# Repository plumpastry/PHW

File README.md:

# **P**lum's **H**ard**W**are

PHW-Board#-Part#-Revision#

## PHW-1-1-2:

NFC smartwatch development board

## PHW-1-1-1:

NFC smartwatch original board - infeasible manual assembly due to STM32WL

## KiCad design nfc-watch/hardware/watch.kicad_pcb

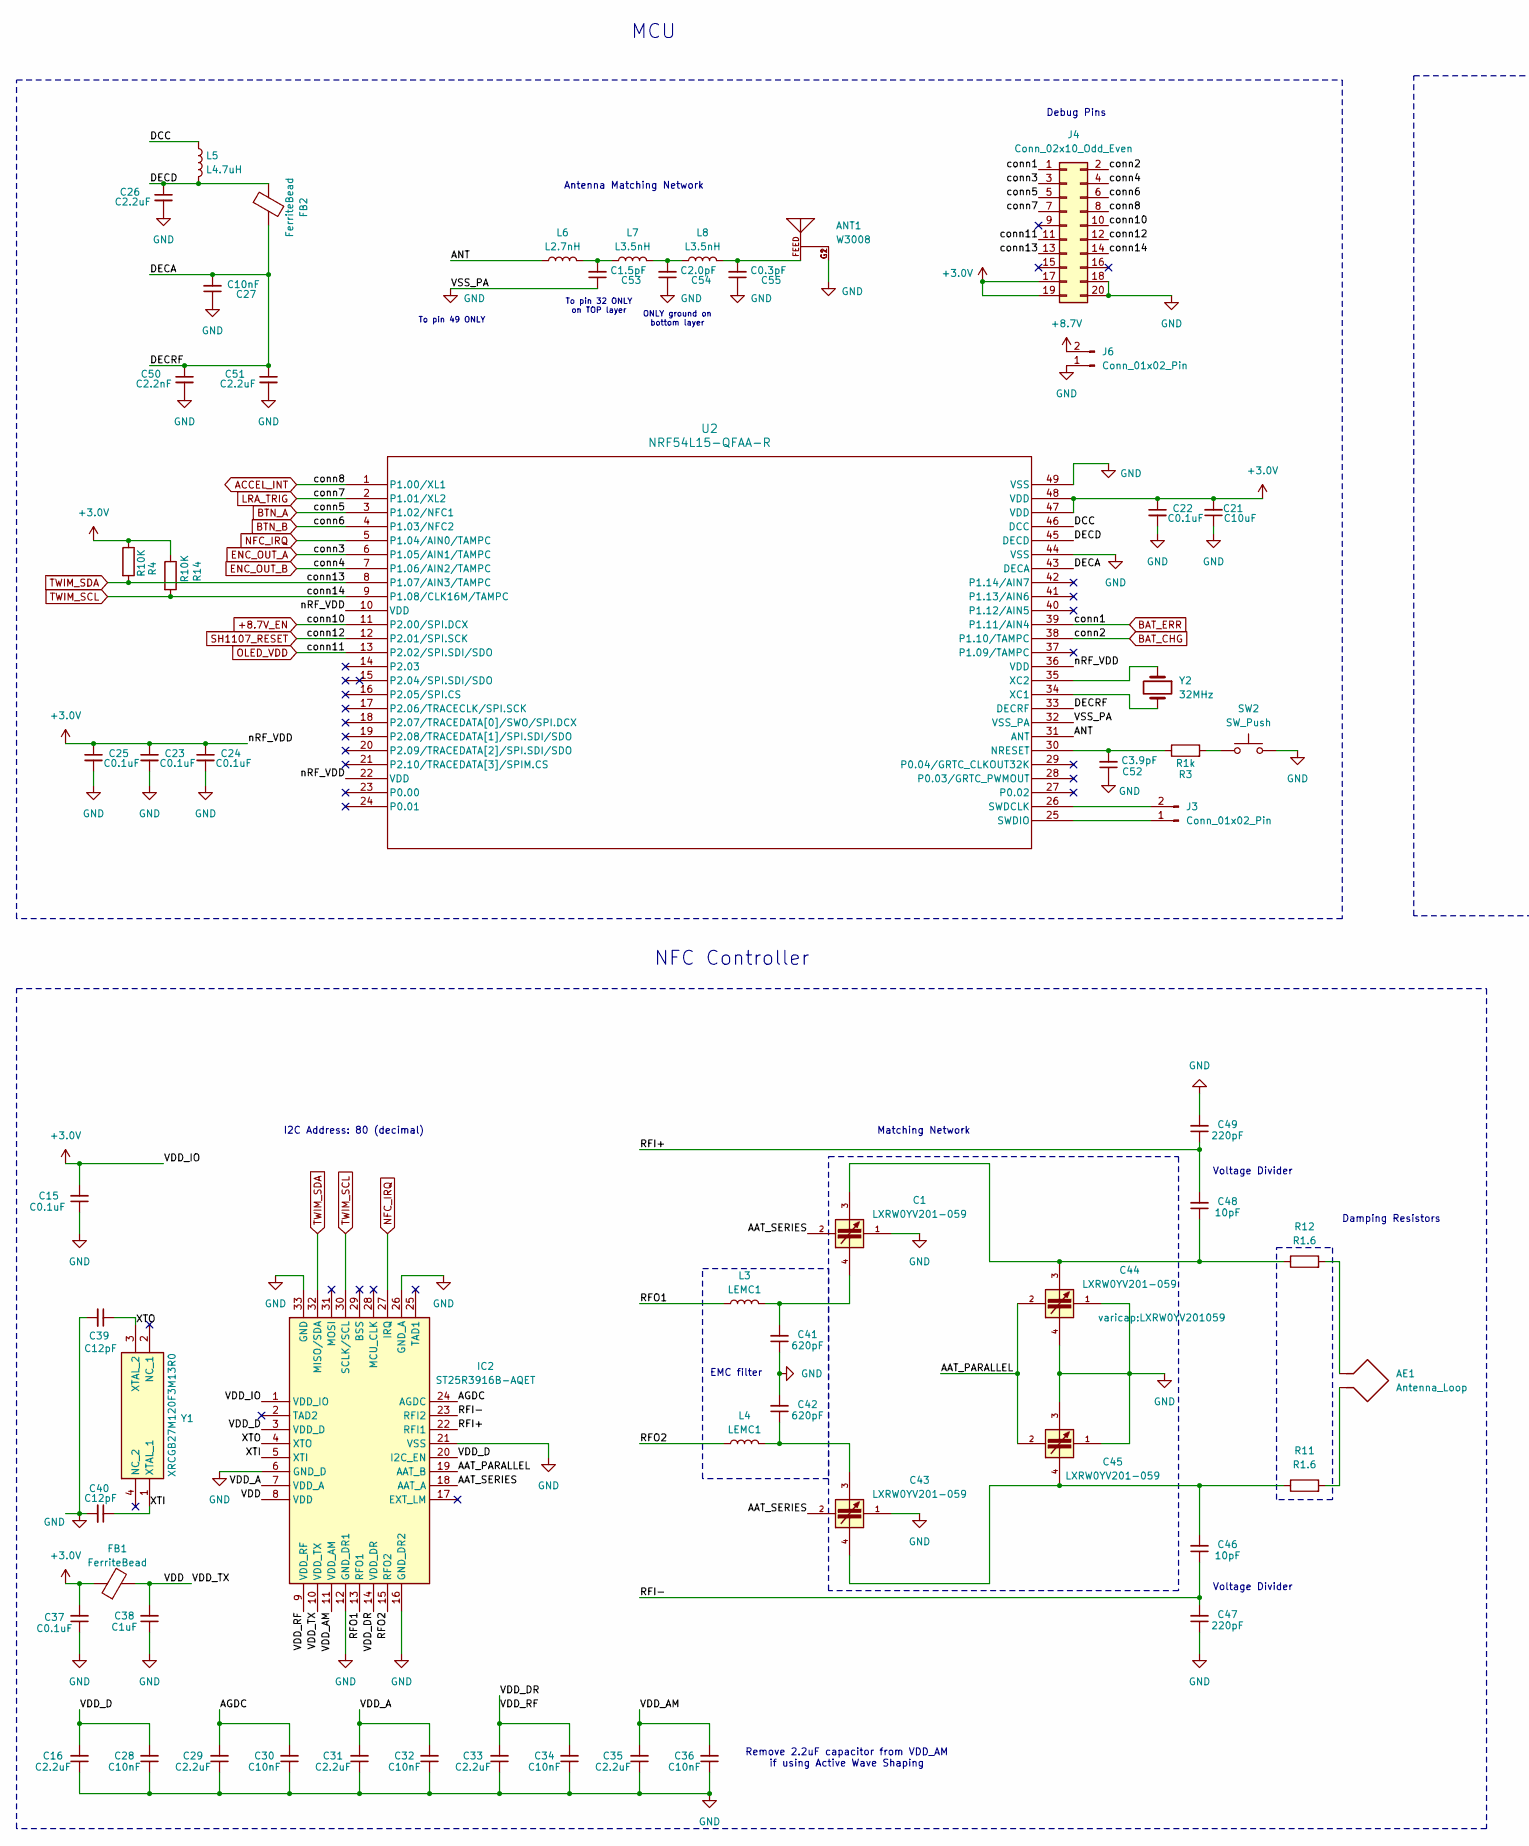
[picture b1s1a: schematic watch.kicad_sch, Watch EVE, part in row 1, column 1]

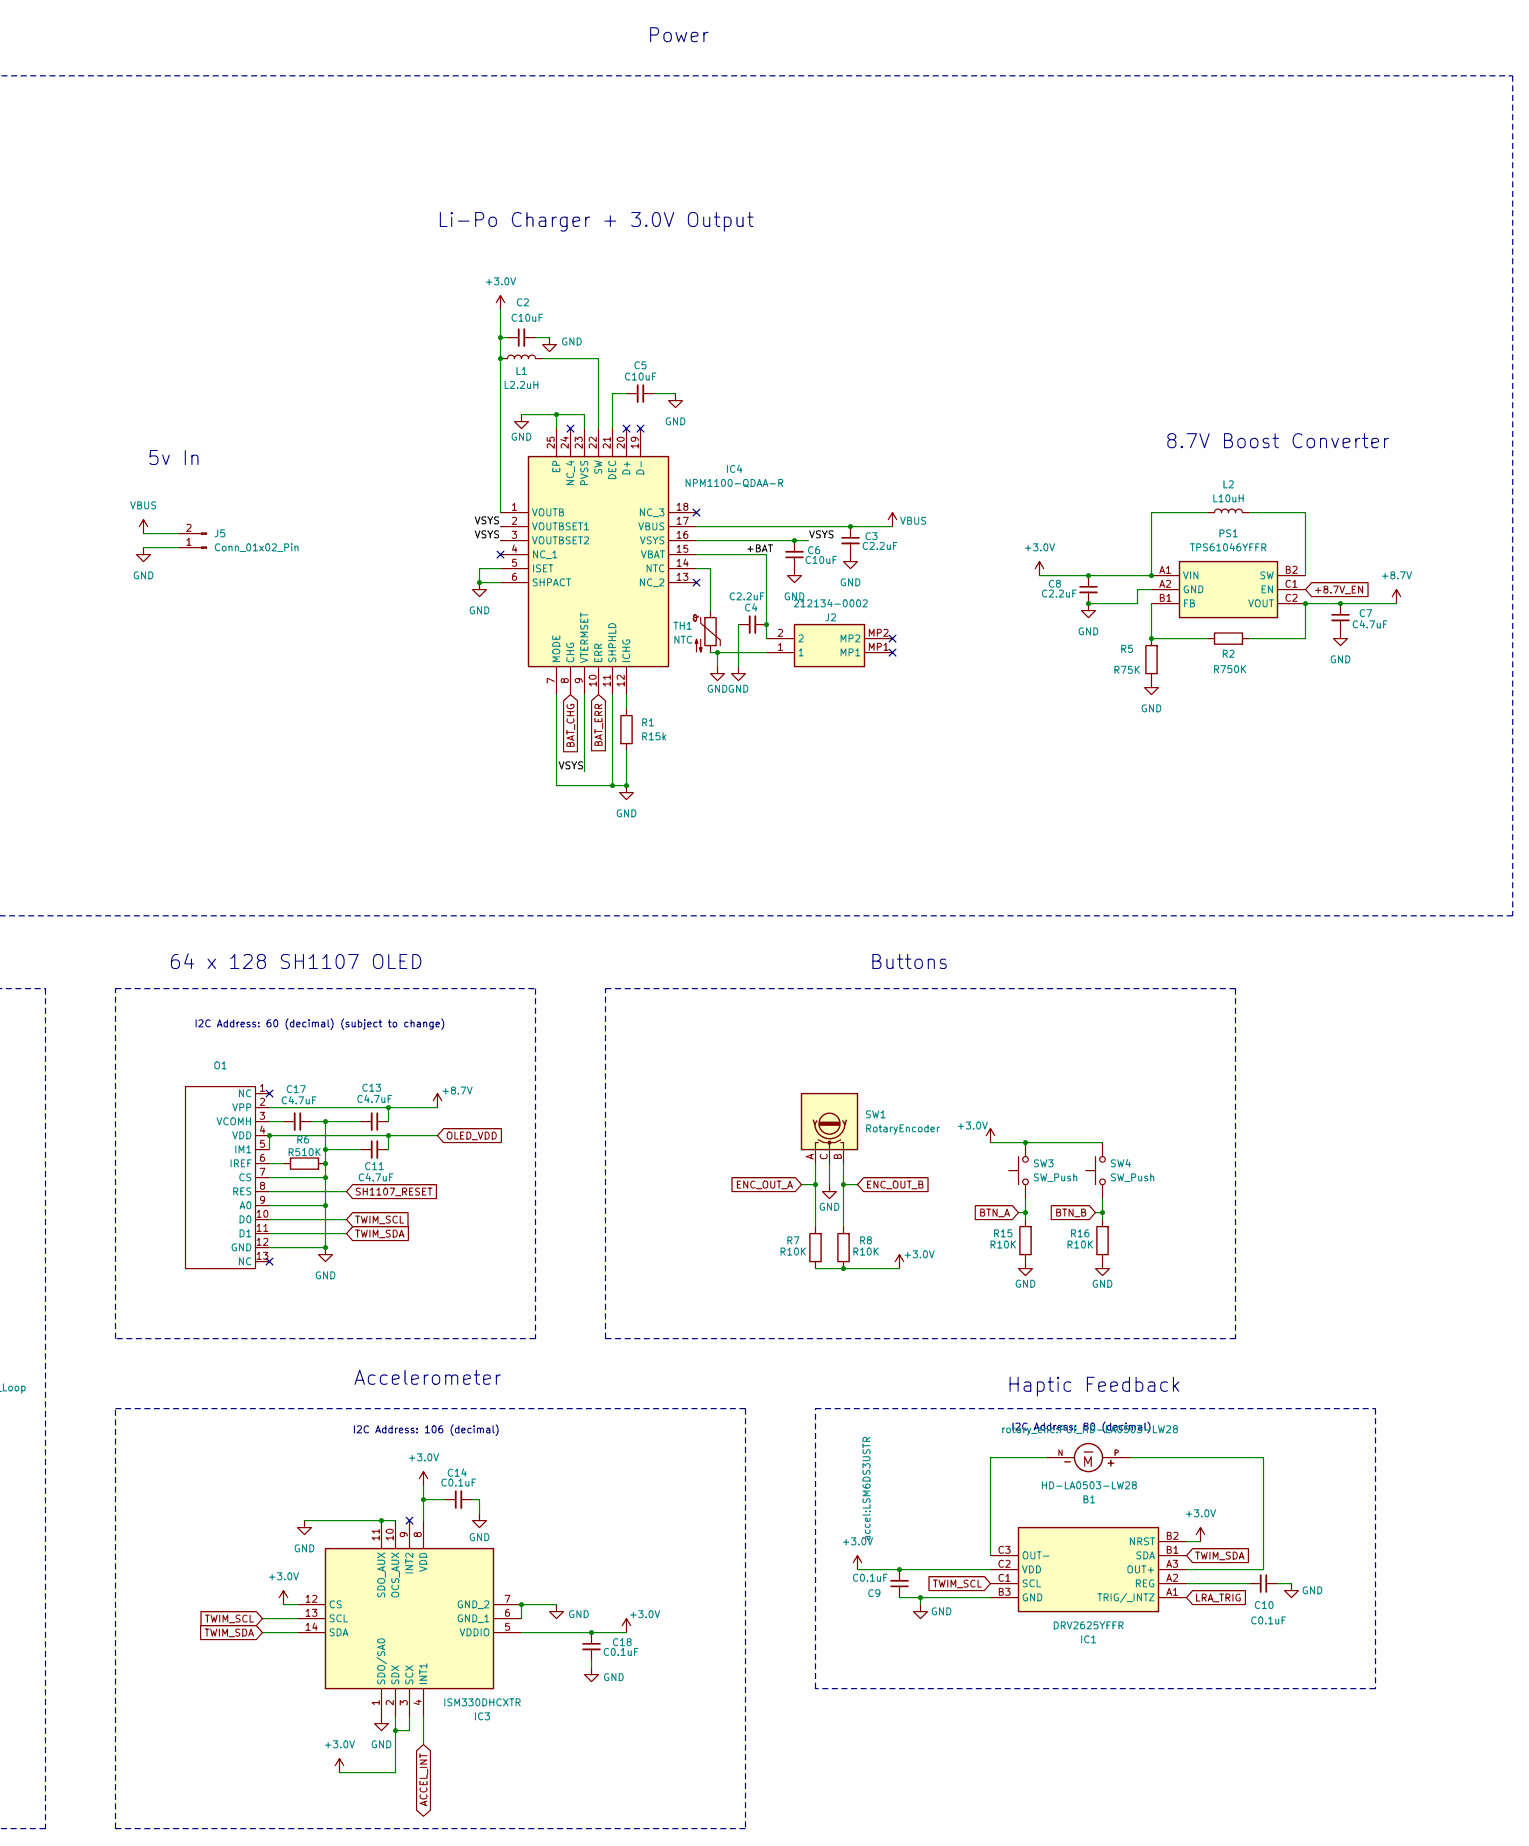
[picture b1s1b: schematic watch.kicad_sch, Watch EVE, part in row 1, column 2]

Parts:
AE1: Antenna_Loop; C_0603_1608Metric
ANT1: W3008; ANTENNA_W3008
B1: HD-LA0503-LW28; PUI_HD-LA0503-LW28; PARTREV A
C1, C43, C44, C45: LXRW0YV201-059; LXRW0YV201059; PARTREV July, 2018
C2, C5, C6, C21: C10uF; C_0402_1005Metric
C3, C4, C8, C26, C51: C2.2uF; C_0402_1005Metric
C7, C11, C13, C17: C4.7uF; C_0402_1005Metric
C9, C10, C14, C15, C18, C22, C23, C24, C25, C37: C0.1uF; C_0402_1005Metric
C16, C29, C31, C33, C35: C2.2uF; C_0201_0603Metric
C27, C28, C30, C32, C34, C36: C10nF; C_0201_0603Metric
C38: C1uF; C_0402_1005Metric
C39, C40: C12pF; C_0402_1005Metric
C41, C42: 620pF; C_0402_1005Metric
C46, C48: 10pF; C_0402_1005Metric
C47, C49: 220pF; C_0402_1005Metric
C50: C2.2nF; C_0402_1005Metric
C52: C3.9pF; C_0402_1005Metric
C53: C1.5pF; C_0201_0603Metric
C54: C2.0pF; C_0201_0603Metric
C55: C0.3pF; C_0201_0603Metric
FB1, FB2: FerriteBead; L_0402_1005Metric
IC1: DRV2625YFFR; BGA9C40P3X3_147X133X62; Mouser Part Number 595-DRV2625YFFR
IC2: ST25R3916B-AQET; QFN50P500X500X60-33N-D; Mouser Part Number 511-ST25R3916B-AQET
IC3: ISM330DHCXTR; LSM6DS3USTR; Mouser Part Number 511-ISM330DHCXTR
IC4: NPM1100-QDAA-R; QFN50P400X400X90-25N-D; Mouser Part Number 949-NPM1100-QDAA-R
J2: 212134-0002; 2121340002; Mouser Part Number 538-212134-0002
J3, J5, J6: Conn_01x02_Pin; PinHeader_1x02_P2.54mm_Vertical
J4: Conn_02x10_Odd_Even; PinHeader_2x10_P2.54mm_Vertical
L1: L2.2uH; L_0805_2012Metric
L2: L10uH; L_1008_2520Metric
L3, L4: LEMC1; L_0402_1005Metric
L5: L4.7uH; L_0603_1608Metric
L6: L2.7nH; L_0201_0603Metric
L7, L8: L3.5nH; L_0201_0603Metric
O1: P0.7_FPC
PS1: TPS61046YFFR; BGA6C40P2X3_88X123X62; Mouser Part Number 595-TPS61046YFFR
R1: R15k; R_0402_1005Metric
R2: R750K; R_0402_1005Metric
R3: R1k; C_0402_1005Metric
R4, R7, R8, R14, R15, R16: R10K; R_0402_1005Metric
R5: R75K; R_0402_1005Metric
R6: R510K; R_0402_1005Metric
R11, R12: R1.6; R_0402_1005Metric
SW1: RotaryEncoder; alps_ec05e
SW2, SW3, SW4: SW_Push; SW_B3U-1100P
TH1: NTC; C_0201_0603Metric
U2: NRF54L15-QFAA-R; QFN-48-1EP_6x6mm_P0.4mm_EP4.6x4.6mm
Y1: XRCGB27M120F3M13R0; XRCGB; Mouser Part Number 81-XRCGB27M120F3M13R
Y2: 32MHz; Crystal_SMD_2016-4Pin_2.0x1.6mm

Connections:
+3.0V: C2.1, C8.1, C9.2, C14.1, C15.2, C18.1, C21.2, C22.1, C23.1, C24.1, C25.1, C37.2, FB1.1, IC1.B2 (NRST), IC1.C2 (VDD), IC2.1 (VDD_IO), IC3.2 (SDX), IC3.3 (SCX), IC3.5 (VDDIO), IC3.8 (VDD), IC3.12 (CS), IC4.1 (VOUTB), J4.17, J4.19, L1.1, L2.1, PS1.A1 (VIN), R4.1, R7.1, R8.1, R14.1, SW3.2, SW4.2, U2.10 (VDD), U2.22 (VDD), U2.36 (VDD), U2.47 (VDD), U2.48 (VDD)
+8.7V: C7.1, C13.1, J6.2, O1.2 (VPP), PS1.C2 (VOUT), R2.2
+8.7V_EN: J4.10, PS1.C1 (EN), U2.11 (P2.00/SPI.DCX)
/+BAT: C4.2, IC4.15 (VBAT), J2.2
/AAT_PARALLEL: C44.2, C45.2, IC2.19 (AAT_B)
/AAT_SERIES: C1.2, C43.2, IC2.18 (AAT_A)
/AGDC: C29.2, C30.2, IC2.24 (AGDC)
/ANT: L6.1, U2.31 (ANT)
/DCC: L5.1, U2.46 (DCC)
/DECA: C27.2, C50.1, C51.1, FB2.2, U2.33 (DECRF), U2.43 (DECA)
/DECD: C26.1, FB2.1, L5.2, U2.45 (DECD)
/RFI+: C48.2, C49.1, IC2.22 (RFI1)
/RFI-: C46.1, C47.2, IC2.23 (RFI2)
/RFO1: IC2.13 (RFO1), L3.1
/RFO2: IC2.15 (RFO2), L4.1
/VDD: C38.2, FB1.2, IC2.8 (VDD), IC2.10 (VDD_TX)
/VDD_A: C31.2, C32.2, IC2.7 (VDD_A)
/VDD_AM: C35.2, C36.2, IC2.11 (VDD_AM)
/VDD_D: C16.2, C28.2, IC2.3 (VDD_D), IC2.20 (I2C_EN)
/VDD_DR: C33.2, C34.2, IC2.9 (VDD_RF), IC2.14 (VDD_DR)
/VSYS: C6.2, IC4.2 (VOUTBSET1), IC4.3 (VOUTBSET2), IC4.9 (VTERMSET), IC4.16 (VSYS)
/XTI: C40.1, IC2.5 (XTI), Y1.1 (XTAL_1)
/XTO: C39.1, IC2.4 (XTO), Y1.3 (XTAL_2)
ACCEL_INT: IC3.4 (INT1), J4.8, U2.1 (P1.00/XL1)
BAT_CHG: IC4.8 (CHG), J4.2, U2.38 (P1.10/TAMPC)
BAT_ERR: IC4.10 (ERR), J4.1, U2.39 (P1.11/AIN4)
BTN_A: J4.5, R15.2, SW3.1, U2.3 (P1.02/NFC1)
BTN_B: J4.6, R16.2, SW4.1, U2.4 (P1.03/NFC2)
ENC_OUT_A: J4.3, R7.2, SW1.A, U2.6 (P1.05/AIN1/TAMPC)
ENC_OUT_B: J4.4, R8.2, SW1.B, U2.7 (P1.06/AIN2/TAMPC)
GND: ANT1.G1, ANT1.G2, C1.1, C2.2, C3.2, C4.1, C5.1, C6.1, C7.2, C8.2, C9.1, C10.1, C11.1, C13.2, C14.2, C15.1, C16.1, C17.1, C18.2, C21.1, C22.2, C23.2, C24.2, C25.2, C26.2, C27.1, C28.1, C29.1, C30.1, C31.1, C32.1, C33.1, C34.1, C35.1, C36.1, C37.1, C38.1, C39.2, C40.2, C41.1, C42.2, C43.1, C44.1, C44.4, C45.1, C45.3, C47.1, C49.2, C50.2, C51.2, C52.1, C53.1, C54.1, C55.1, IC1.B3 (GND), IC2.6 (GND_D), IC2.12 (GND_DR1), IC2.16 (GND_DR2), IC2.21 (VSS), IC2.26 (GND_A), IC2.33 (GND), IC3.1 (SDO/SA0), IC3.6 (GND_1), IC3.7 (GND_2), IC3.10 (OCS_AUX), IC3.11 (SDO_AUX), IC4.5 (ISET), IC4.6 (SHPACT), IC4.7 (MODE), IC4.11 (SHPHLD), IC4.23 (PVSS), IC4.25 (EP), J2.1, J4.18, J4.20, J5.1, J6.1, O1.7 (CS), O1.9 (A0), O1.12 (GND), PS1.A2 (GND), R1.2, R5.1, R6.2, R15.1, R16.1, SW1.C, SW2.2, TH1.2, U2.32 (VSS_PA), U2.44 (VSS), U2.49 (VSS)
LRA_TRIG: IC1.A1 (TRIG/_INTZ), J4.7, U2.2 (P1.01/XL2)
NFC_IRQ: IC2.27 (IRQ), U2.5 (P1.04/AIN0/TAMPC)
unnamed: AE1.1, R12.2
unnamed: AE1.2, R11.2
unnamed: ANT1.FEED, C55.2, L8.2
unnamed: C1.3, C44.3, C48.1, R12.1
unnamed: C1.4, C41.2, L3.2
unnamed: C42.1, C43.3, L4.2
unnamed: C43.4, C45.4, C46.2, R11.1
unnamed: C53.2, L6.2, L7.1
unnamed: C54.2, L7.2, L8.1
unnamed: B1.P, IC1.A3 (OUT+)
unnamed: B1.N, IC1.C3 (OUT-)
unnamed: C10.2, IC1.A2 (REG)
unnamed: C5.2, IC4.21 (DEC)
unnamed: IC4.12 (ICHG), R1.1
unnamed: IC4.14 (NTC), TH1.1
unnamed: IC4.22 (SW), L1.2
unnamed: J3.1, U2.25 (SWDIO)
unnamed: J3.2, U2.26 (SWDCLK)
unnamed: O1.6 (IREF), R6.1
unnamed: C17.2, O1.3 (VCOMH)
unnamed: PS1.B1 (FB), R2.1, R5.2
unnamed: L2.2, PS1.B2 (SW)
unnamed: R3.2, SW2.1
unnamed: C52.2, R3.1, U2.30 (NRESET)
unnamed: U2.34 (XC1), Y2.2
unnamed: U2.35 (XC2), Y2.1
OLED_VDD: C11.2, J4.11, O1.4 (VDD), O1.5 (IM1), U2.13 (P2.02/SPI.SDI/SDO)
SH1107_RESET: J4.12, O1.8 (RES), U2.12 (P2.01/SPI.SCK)
TWIM_SCL: IC1.C1 (SCL), IC2.30 (SCLK/SCL), IC3.13 (SCL), J4.14, O1.10 (D0), R14.2, U2.9 (P1.08/CLK16M/TAMPC)
TWIM_SDA: IC1.B1 (SDA), IC2.32 (MISO/SDA), IC3.14 (SDA), J4.13, O1.11 (D1), R4.2, U2.8 (P1.07/AIN3/TAMPC)
VBUS: C3.1, IC4.17 (VBUS), J5.2

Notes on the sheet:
64 x 128 SH1107 OLED
I2C Address: 80 (decimal)
Damping Resistors
Matching Network
8.7V Boost Converter
I2C Address: 106 (decimal)
Buttons
To pin 49 ONLY
Accelerometer
Power
MCU
Haptic Feedback
To pin 32 ONLY on TOP layer
ONLY ground on bottom layer
Antenna Matching Network
Li-Po Charger + 3.0V Output
Debug Pins
5v In
NFC Controller
EMC filter
Voltage Divider
Remove 2.2uF capacitor from VDD_AM if using Active Wave Shaping
I2C Address: 60 (decimal) (subject to change)

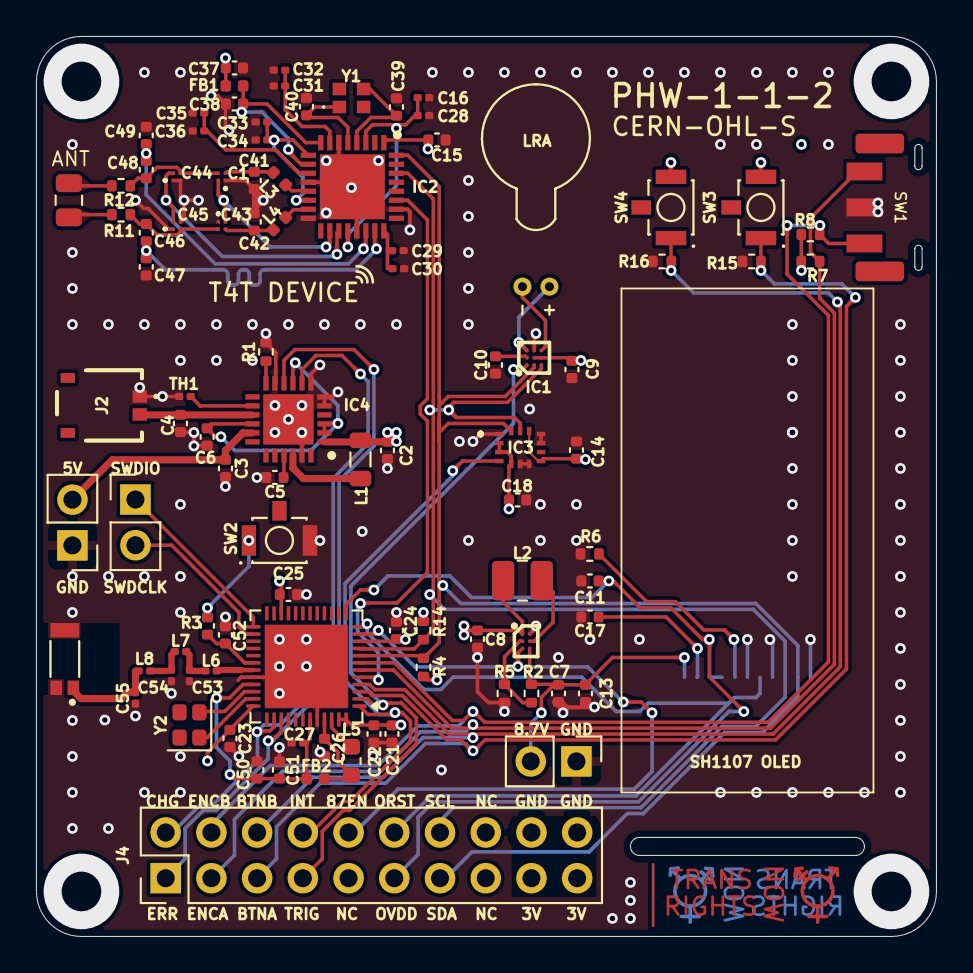
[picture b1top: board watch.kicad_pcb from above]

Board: 4 copper layers, 50.0 x 50.0 mm, 99 parts (0 on the bottom side), 64 nets.

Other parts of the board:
TRNSRTS: Trans Rights now Front
TRNSRTS#2: Trans Rights now Back

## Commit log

2026-02-16 Fix typo
2026-02-17 Initial File Commit
2026-02-17 Added Interactive BOM
2026-02-17 Added PHW-1-1-1 Archive
2026-02-17 Added PHW-1-1-1 to readme
2026-02-17 Created default cargo package
2026-02-17 Add CERN Open Hardware License
2026-02-17 Add AGPL license
2026-02-17 Update AGPL location
2026-03-19 Initial firmware setup
    Added hello world board firmware and gitignore
2026-03-20 Initial DRV2625 driver
    Barebones DRV2625 driver library added
2026-03-22 Updated DRV2625 crate info

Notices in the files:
nfc-watch/hardware/watch.kicad_pcb:
CERN-OHL-S
